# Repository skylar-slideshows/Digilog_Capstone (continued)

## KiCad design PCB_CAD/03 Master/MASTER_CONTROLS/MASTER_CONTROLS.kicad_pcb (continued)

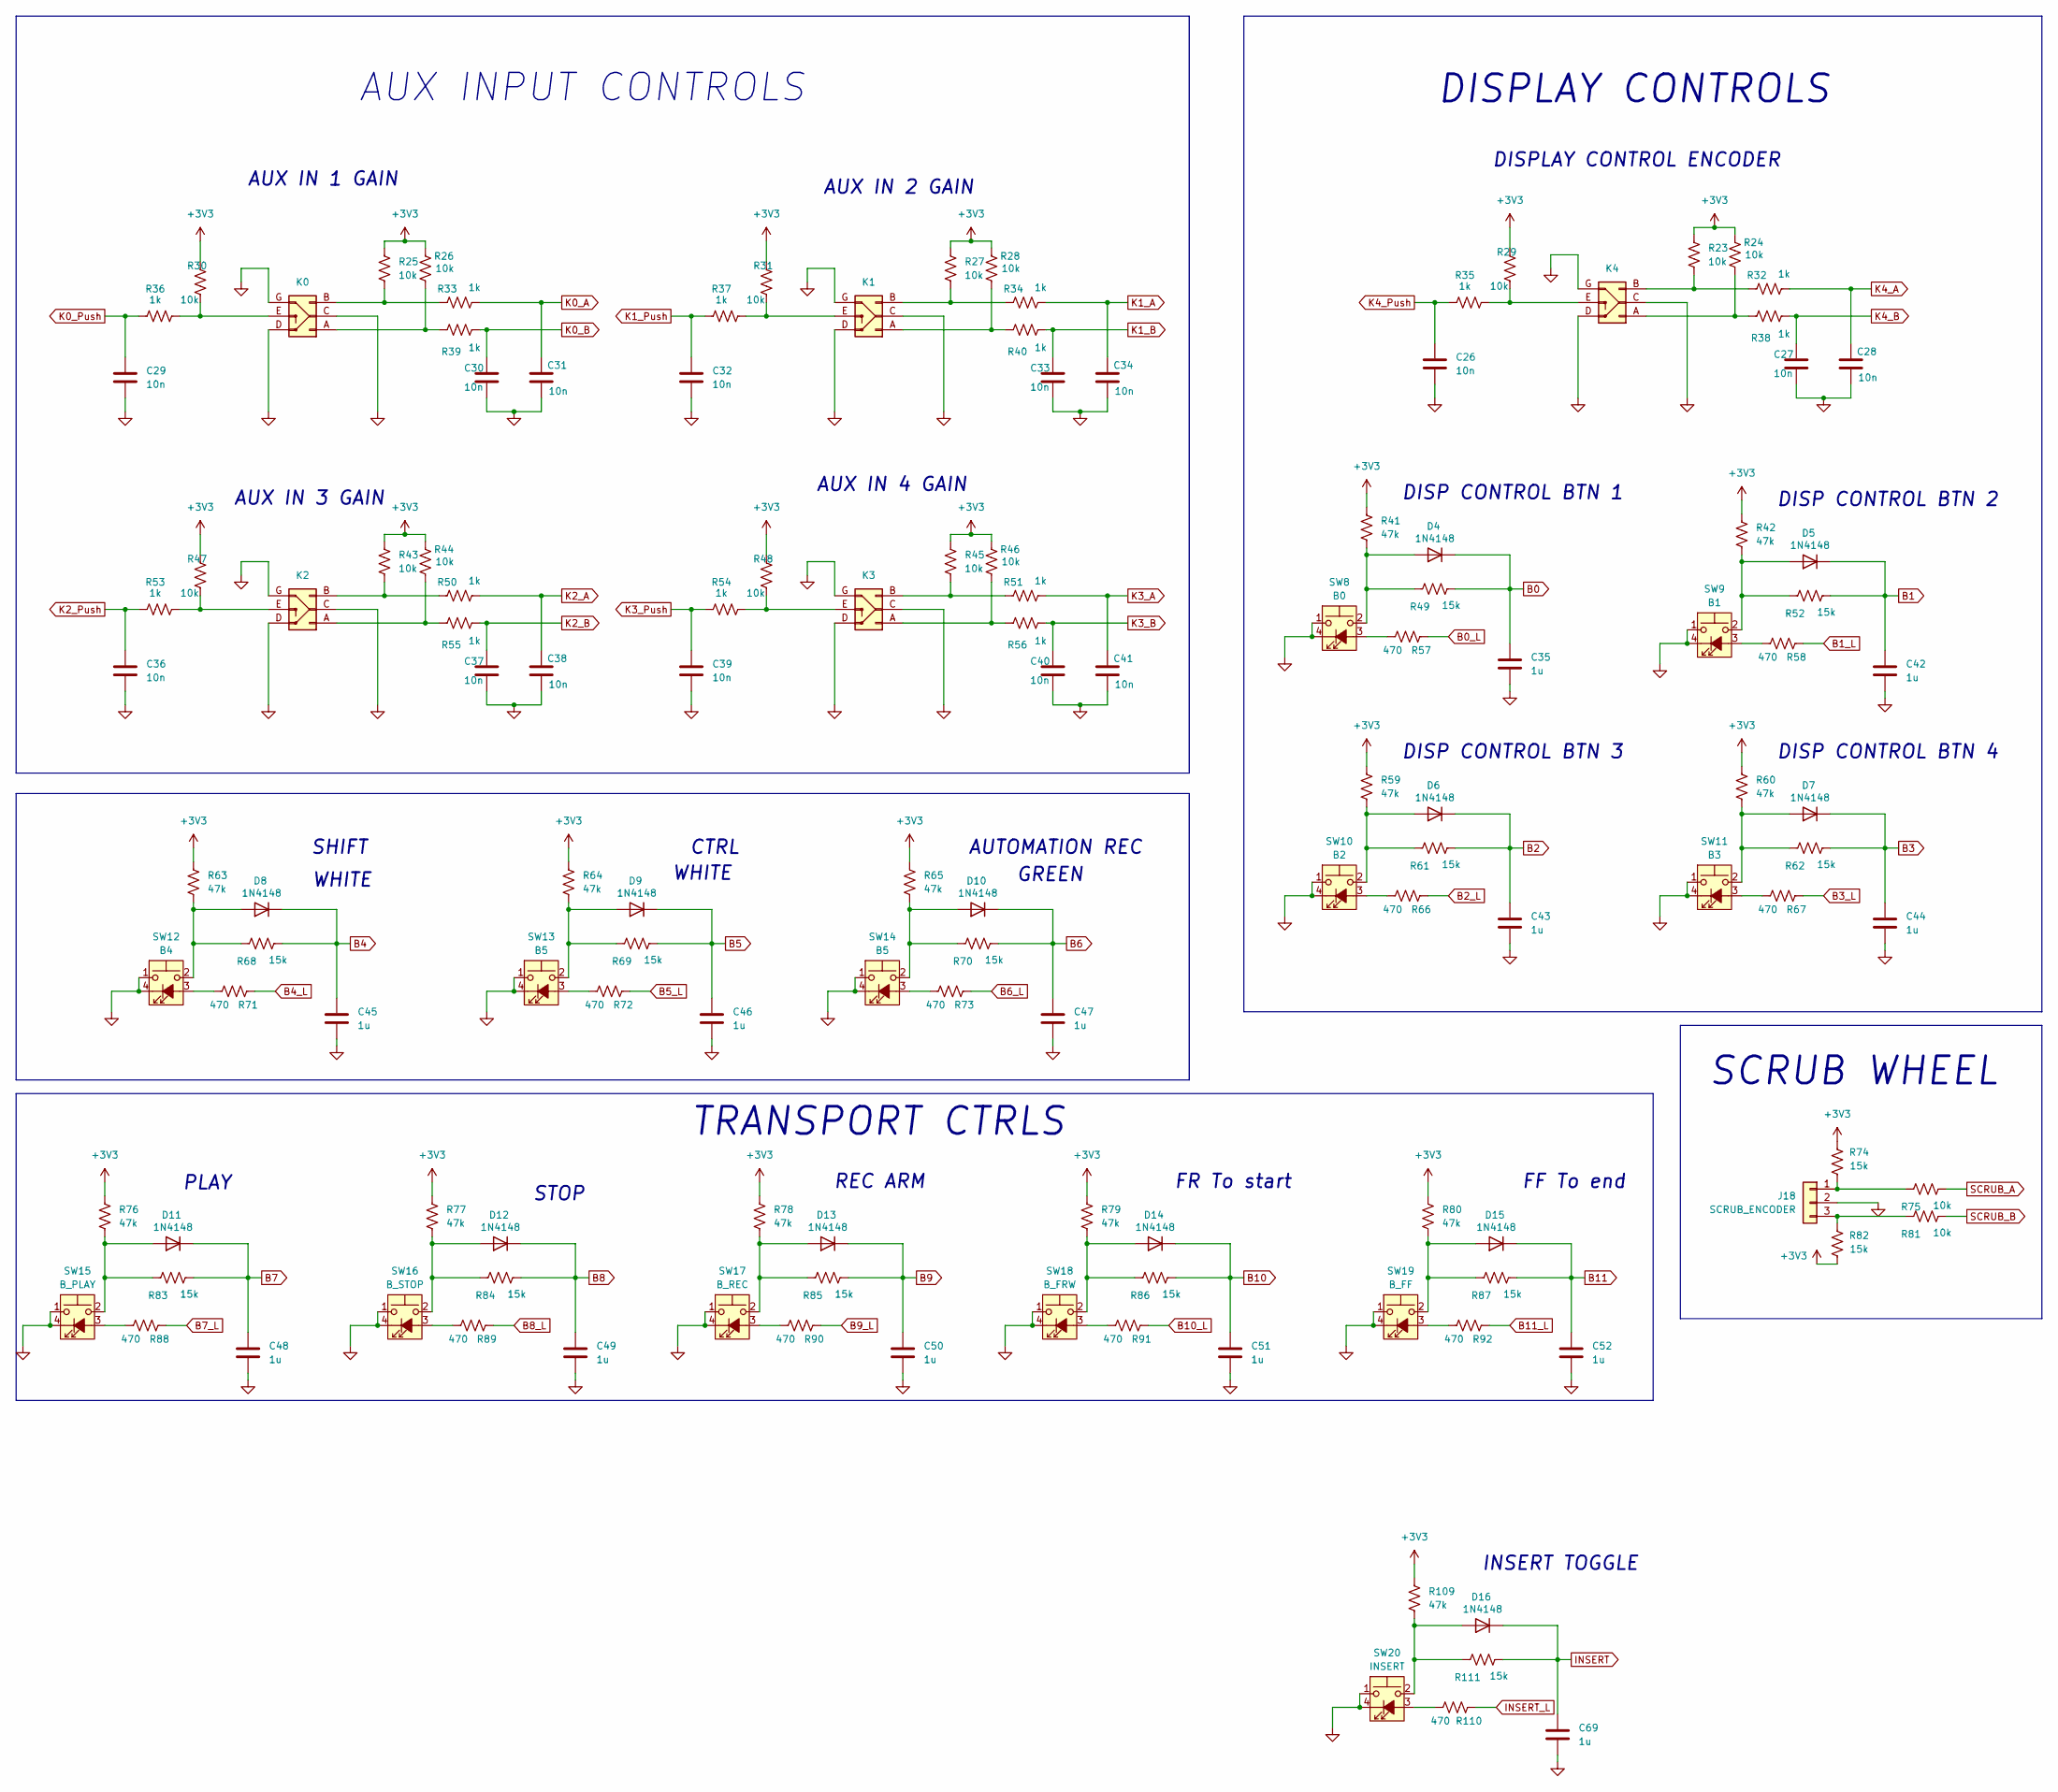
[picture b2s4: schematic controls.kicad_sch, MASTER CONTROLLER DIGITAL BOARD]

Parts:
C26, C27, C28, C29, C30, C31, C32, C33, C34, C36, C37, C38, C39, C40, C41: 10n; C_0402_1005Metric; LCSC C1524
C35, C42, C43, C44, C45, C46, C47, C48, C49, C50, C51, C52, C69: 1u; C_0603_1608Metric; LCSC C15849
D4, D5, D6, D7, D8, D9, D10, D11, D12, D13, D14, D15, D16: 1N4148; D_SOD-323; LCSC C2128
J18: SCRUB_ENCODER; PinHeader_1x03_P2.54mm_Vertical; Part Number 1-0301FBV0T; LCSC DNP
R23, R24, R25, R26, R27, R28, R29, R30, R31, R43, R44, R45, R46, R47, R48, R75, R81: 10k; R_0603_1608Metric; LCSC C25804
R32, R33, R34, R35, R36, R37, R38, R39, R40, R50, R51, R53, R54, R55, R56: 1k; R_0603_1608Metric; LCSC C21190
R41, R42, R59, R60, R63, R64, R65, R76, R77, R78, R79, R80, R109: 47k; R_0603_1608Metric; LCSC C25819
R49, R52, R61, R62, R68, R69, R70, R74, R82, R83, R84, R85, R86, R87, R111: 15k; R_0603_1608Metric; LCSC C22809
R57, R58, R66, R67, R71, R72, R73, R88, R89, R90, R91, R92, R110: 470; R_0603_1608Metric; LCSC C25241
SW3: K4; EC11J0924411; LCSC DNP
SW4: K0; EC11J0924411; LCSC DNP
SW5: K1; EC11J0924411; LCSC DNP
SW6: K2; EC11J0924411; LCSC DNP
SW7: K3; EC11J0924411; LCSC DNP
SW8: B0; CFPB-1CC-4W6_LOWPROF; LCSC DNP
SW9: B1; CFPB-1CC-4W6_LOWPROF; LCSC DNP
SW10: B2; CFPB-1CC-4W6_LOWPROF; LCSC DNP
SW11: B3; CFPB-1CC-4W6_LOWPROF; LCSC DNP
SW12: B4; CFPB-1CC-4W6_LOWPROF; LCSC DNP
SW13, SW14: B5; CFPB-1CC-4W6_LOWPROF; LCSC DNP
SW15: B_PLAY; CFPB-1CC-4W2; LCSC DNP
SW16: B_STOP; CFPB-1CC-4W2; LCSC DNP
SW17: B_REC; CFPB-1CC-4W2; LCSC DNP
SW18: B_FRW; CFPB-1CC-4W2; LCSC DNP
SW19: B_FF; CFPB-1CC-4W2; LCSC DNP
SW20: INSERT; CFPB-1CC-4W6_LOWPROF; LCSC DNP

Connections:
+3V3: R23.1, R24.1, R25.1, R26.1, R27.1, R28.1, R29.1, R30.1, R31.1, R41.1, R42.1, R43.1, R44.1, R45.1, R46.1, R47.1, R48.1, R59.1, R60.1, R63.1, R64.1, R65.1, R74.2, R76.1, R77.1, R78.1, R79.1, R80.1, R82.1, R109.1; also elsewhere on the board
B0: C35.1, D4.1 (K), R49.2; also elsewhere on the board
B0_L: R57.2; also elsewhere on the board
B1: C42.1, D5.1 (K), R52.2; also elsewhere on the board
B1_L: R58.2; also elsewhere on the board
B2: C43.1, D6.1 (K), R61.2; also elsewhere on the board
B2_L: R66.2; also elsewhere on the board
B3: C44.1, D7.1 (K), R62.2; also elsewhere on the board
B3_L: R67.2; also elsewhere on the board
B4: C45.1, D8.1 (K), R68.2; also elsewhere on the board
B4_L: R71.2; also elsewhere on the board
B5: C46.1, D9.1 (K), R69.2; also elsewhere on the board
B5_L: R72.2; also elsewhere on the board
B6: C47.1, D10.1 (K), R70.2; also elsewhere on the board
B6_L: R73.2; also elsewhere on the board
B7: C48.1, D11.1 (K), R83.2; also elsewhere on the board
B7_L: R88.2; also elsewhere on the board
B8: C49.1, D12.1 (K), R84.2; also elsewhere on the board
B8_L: R89.2; also elsewhere on the board
B9: C50.1, D13.1 (K), R85.2; also elsewhere on the board
B9_L: R90.2; also elsewhere on the board
B10: C51.1, D14.1 (K), R86.2; also elsewhere on the board
B10_L: R91.2; also elsewhere on the board
B11: C52.1, D15.1 (K), R87.2; also elsewhere on the board
B11_L: R92.2; also elsewhere on the board
GND: C26.2, C27.2, C28.2, C29.2, C30.2, C31.2, C32.2, C33.2, C34.2, C35.2, C36.2, C37.2, C38.2, C39.2, C40.2, C41.2, C42.2, C43.2, C44.2, C45.2, C46.2, C47.2, C48.2, C49.2, C50.2, C51.2, C52.2, C69.2, J18.2, SW3.C (Pin_2), SW3.D (Pin_4), SW3.G (Pin_6), SW4.C (Pin_2), SW4.D (Pin_4), SW4.G (Pin_6), SW5.C (Pin_2), SW5.D (Pin_4), SW5.G (Pin_6), SW6.C (Pin_2), SW6.D (Pin_4), SW6.G (Pin_6), SW7.C (Pin_2), SW7.D (Pin_4), SW7.G (Pin_6), SW8.1, SW8.4 (K), SW9.1, SW9.4 (K), SW10.1, SW10.4 (K), SW11.1, SW11.4 (K), SW12.1, SW12.4 (K), SW13.1, SW13.4 (K), SW14.1, SW14.4 (K), SW15.1, SW15.4 (K), SW16.1, SW16.4 (K), SW17.1, SW17.4 (K), SW18.1, SW18.4 (K), SW19.1, SW19.4 (K), SW20.1, SW20.4 (K); also elsewhere on the board
INSERT: C69.1, D16.1 (K), R111.2; also elsewhere on the board
INSERT_L: R110.2; also elsewhere on the board
K0_A: C31.1, R33.2; also elsewhere on the board
K0_B: C30.1, R39.2; also elsewhere on the board
K0_Push: C29.1, R36.1; also elsewhere on the board
K1_A: C34.1, R34.2; also elsewhere on the board
K1_B: C33.1, R40.2; also elsewhere on the board
K1_Push: C32.1, R37.1; also elsewhere on the board
K2_A: C38.1, R50.2; also elsewhere on the board
K2_B: C37.1, R55.2; also elsewhere on the board
K2_Push: C36.1, R53.1; also elsewhere on the board
K3_A: C41.1, R51.2; also elsewhere on the board
K3_B: C40.1, R56.2; also elsewhere on the board
K3_Push: C39.1, R54.1; also elsewhere on the board
K4_A: C28.1, R32.2; also elsewhere on the board
K4_B: C27.1, R38.2; also elsewhere on the board
K4_Push: C26.1, R35.1; also elsewhere on the board
unnamed: D4.2 (A), R41.2, R49.1, SW8.2
unnamed: D5.2 (A), R42.2, R52.1, SW9.2
unnamed: D6.2 (A), R59.2, R61.1, SW10.2
unnamed: D7.2 (A), R60.2, R62.1, SW11.2
unnamed: D8.2 (A), R63.2, R68.1, SW12.2
unnamed: D9.2 (A), R64.2, R69.1, SW13.2
unnamed: D10.2 (A), R65.2, R70.1, SW14.2
unnamed: D11.2 (A), R76.2, R83.1, SW15.2
unnamed: D12.2 (A), R77.2, R84.1, SW16.2
unnamed: D13.2 (A), R78.2, R85.1, SW17.2
unnamed: D14.2 (A), R79.2, R86.1, SW18.2
unnamed: D15.2 (A), R80.2, R87.1, SW19.2
unnamed: D16.2 (A), R109.2, R111.1, SW20.2
unnamed: J18.1, R74.1, R75.1
unnamed: J18.3, R81.1, R82.2
unnamed: R24.2, R38.1, SW3.A (Pin_1)
unnamed: R23.2, R32.1, SW3.B (Pin_3)
unnamed: R29.2, R35.2, SW3.E (Pin_5)
unnamed: R26.2, R39.1, SW4.A (Pin_1)
unnamed: R25.2, R33.1, SW4.B (Pin_3)
unnamed: R30.2, R36.2, SW4.E (Pin_5)
unnamed: R28.2, R40.1, SW5.A (Pin_1)
unnamed: R27.2, R34.1, SW5.B (Pin_3)
unnamed: R31.2, R37.2, SW5.E (Pin_5)
unnamed: R44.2, R55.1, SW6.A (Pin_1)
unnamed: R43.2, R50.1, SW6.B (Pin_3)
unnamed: R47.2, R53.2, SW6.E (Pin_5)
unnamed: R46.2, R56.1, SW7.A (Pin_1)
unnamed: R45.2, R51.1, SW7.B (Pin_3)
unnamed: R48.2, R54.2, SW7.E (Pin_5)
unnamed: R57.1, SW8.3 (A)
unnamed: R58.1, SW9.3 (A)
unnamed: R66.1, SW10.3 (A)
unnamed: R67.1, SW11.3 (A)
unnamed: R71.1, SW12.3 (A)
unnamed: R72.1, SW13.3 (A)
unnamed: R73.1, SW14.3 (A)
unnamed: R88.1, SW15.3 (A)
unnamed: R89.1, SW16.3 (A)
unnamed: R90.1, SW17.3 (A)
unnamed: R91.1, SW18.3 (A)
unnamed: R92.1, SW19.3 (A)
unnamed: R110.1, SW20.3 (A)
SCRUB_A: R75.2; also elsewhere on the board
SCRUB_B: R81.2; also elsewhere on the board

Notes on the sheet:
DISP CONTROL BTN 4
WHITE
AUTOMATION REC
AUX IN 4 GAIN
STOP
TRANSPORT CTRLS
AUX IN 2 GAIN
SCRUB WHEEL
CTRL
FR To start
SHIFT
DISP CONTROL BTN 2
REC ARM
AUX INPUT CONTROLS
INSERT TOGGLE
GREEN
DISP CONTROL BTN 3
PLAY
AUX IN 3 GAIN
AUX IN 1 GAIN
DISPLAY CONTROLS
DISPLAY CONTROL ENCODER
DISP CONTROL BTN 1
FF To end

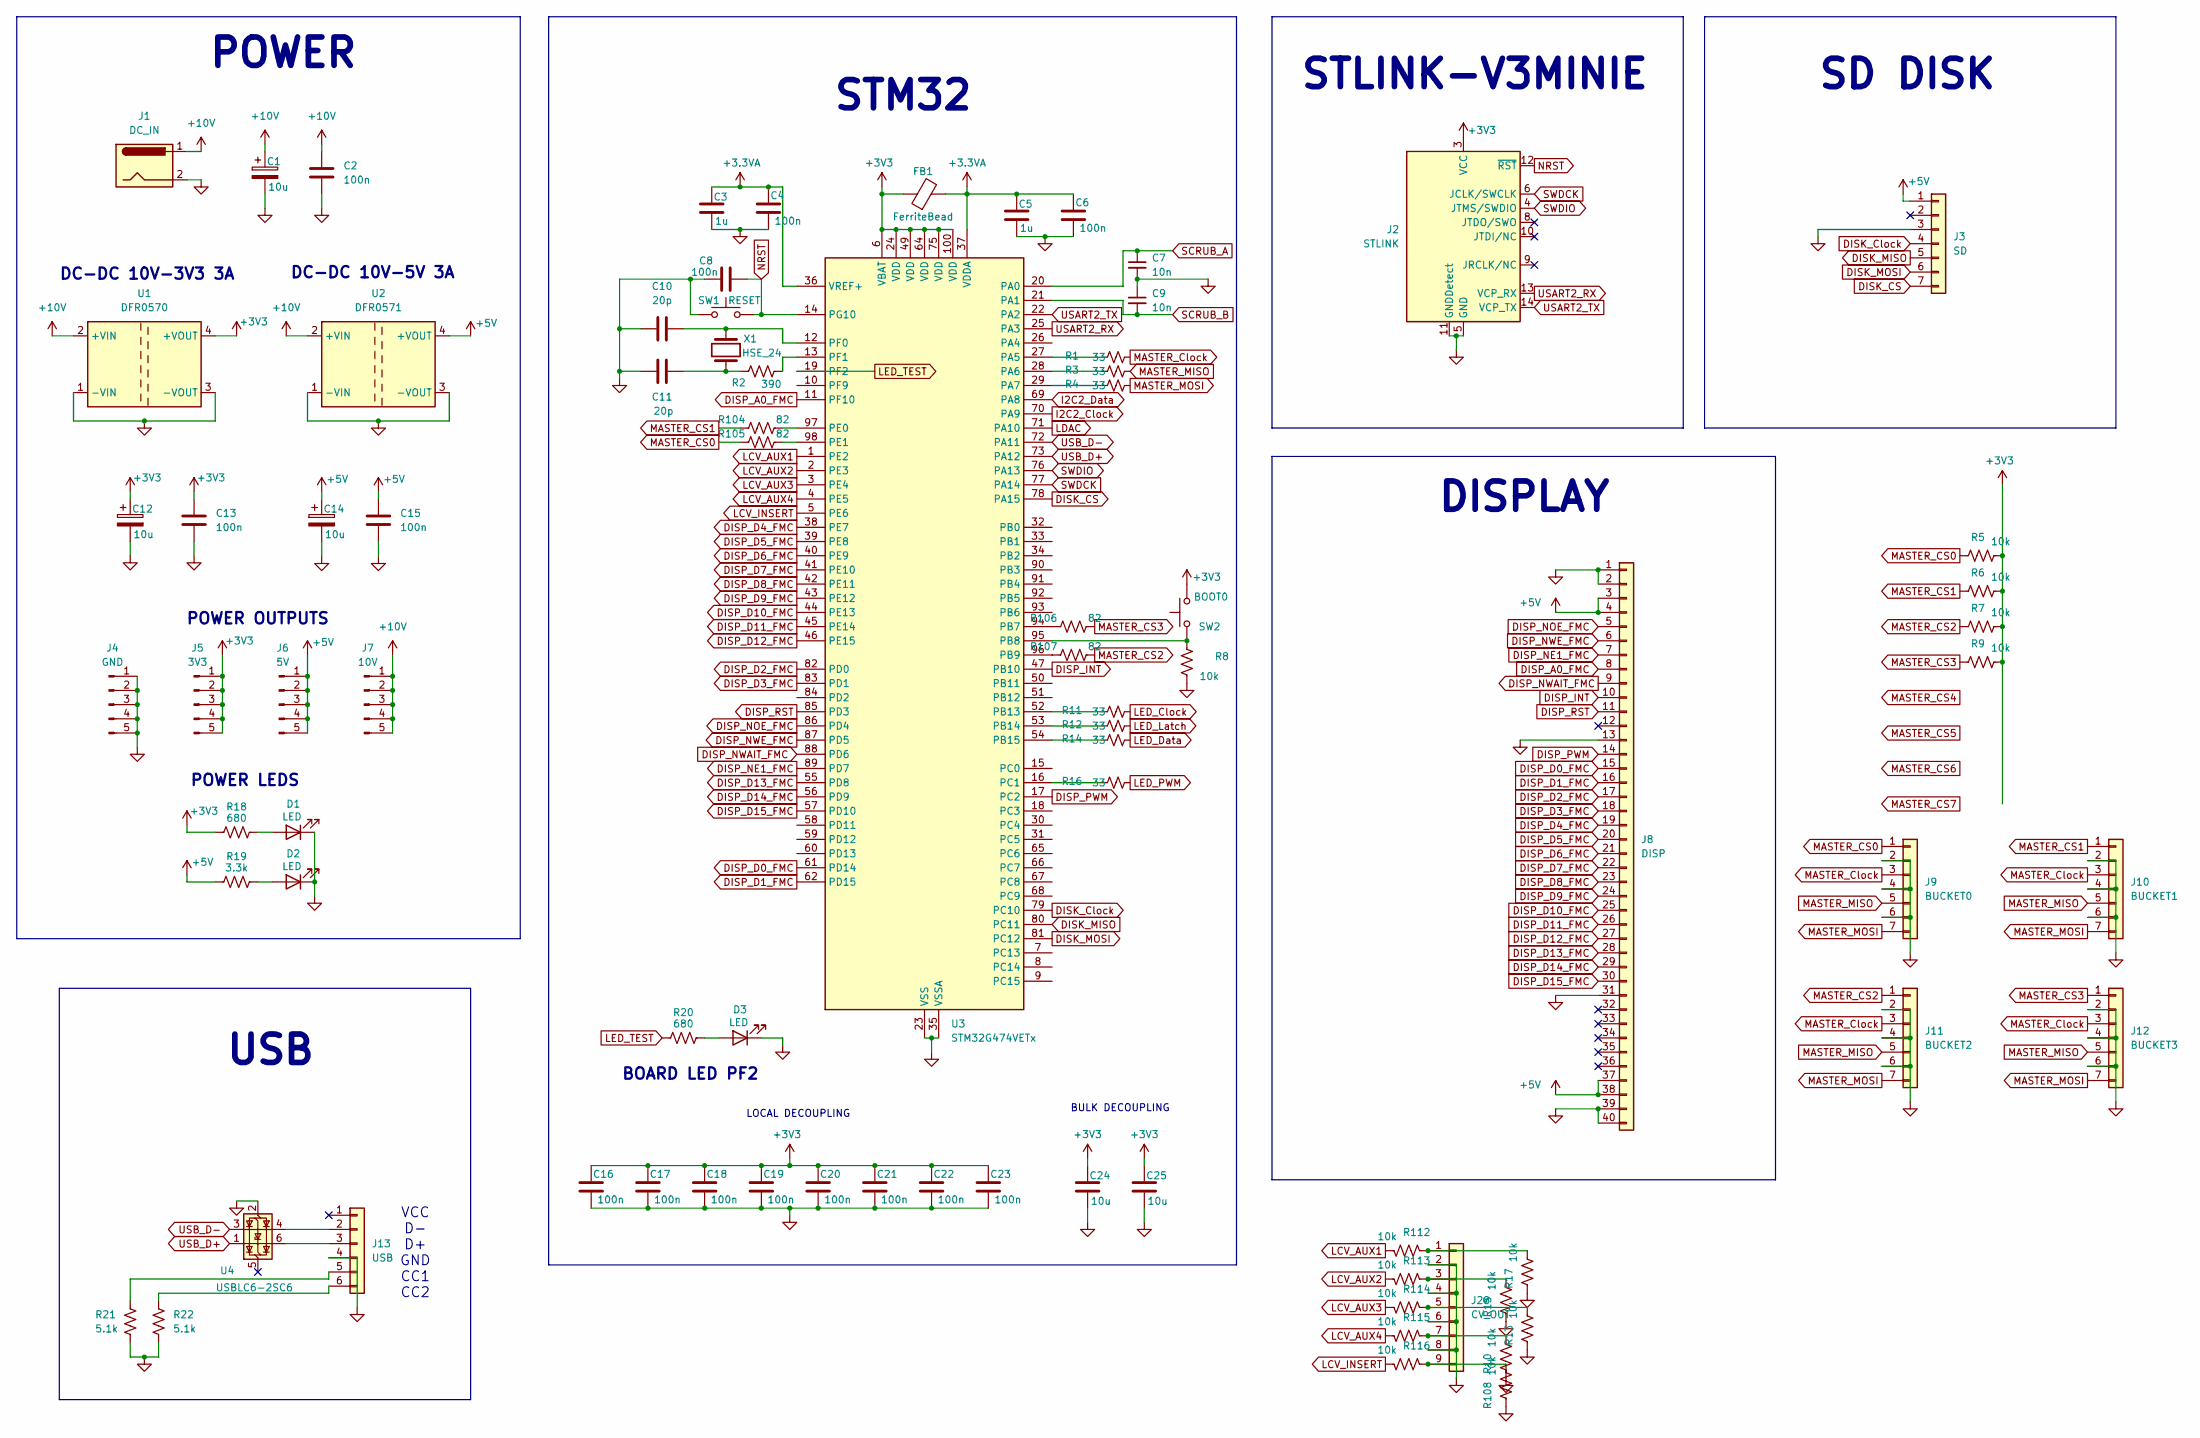
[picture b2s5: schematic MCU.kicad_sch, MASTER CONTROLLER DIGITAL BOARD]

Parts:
C1, C12, C14, C24, C25: 10u; C_1206_3216Metric; LCSC C1849
C2, C4, C6, C8, C13, C15, C16, C17, C18, C19, C20, C21, C22, C23: 100n; C_0603_1608Metric; LCSC C1590
C3, C5: 1u; C_0603_1608Metric; LCSC C15849
C7, C9: 10n; C_0402_1005Metric; LCSC C1524
C10, C11: 20p; C_0603_1608Metric; LCSC C1648
D1, D2, D3: LED; LED_0603_1608Metric; LCSC C12065
FB1: FerriteBead; Ferrite_0603_1608Metric; LCSC C1002
J1: DC_IN; BarrelJack_Horizontal; LCSC DNP
J2: STLINK; FTSH-107-01-L-DV-K-TR; LCSC C5307809
J3: SD; PinHeader_1x07_P2.54mm_Vertical; LCSC DNP
J4: GND; PinSocket_1x05_P2.54mm_Vertical; LCSC DNP
J5: 3V3; PinSocket_1x05_P2.54mm_Vertical; LCSC DNP
J6: 5V; PinSocket_1x05_P2.54mm_Vertical; LCSC DNP
J7: 10V; PinSocket_1x05_P2.54mm_Vertical; LCSC DNP
J8: DISP; GCT_FFC3B07-40-T; LCSC DNP
J9: BUCKET0; PinHeader_1x07_P2.54mm_Vertical; LCSC DNP
J10: BUCKET1; PinHeader_1x07_P2.54mm_Vertical; LCSC DNP
J11: BUCKET2; PinHeader_1x07_P2.54mm_Vertical; LCSC DNP
J12: BUCKET3; PinHeader_1x07_P2.54mm_Vertical; LCSC DNP
J13: USB; PinHeader_1x06_P2.00mm_Vertical; Part Number 1-0601FBV0T; LCSC dnp
J28: CV_OUT; PinHeader_1x09_P2.54mm_Vertical; LCSC DNP
R1, R3, R4, R11, R12, R14, R16: 33; R_0603_1608Metric; LCSC C23140
R2: 390; R_1206_3216Metric; LCSC C4491
R5, R6, R7, R8, R9, R10, R13, R15, R17, R108: 10k; R_0603_1608Metric; LCSC C25804
R18, R20: 680; R_0603_1608Metric; LCSC C23228
R19: 3.3k; R_0603_1608Metric; LCSC C22978
R21, R22: 5.1k; R_0603_1608Metric; LCSC C14677
R104, R105, R106, R107: 82; R_0603_1608Metric; LCSC C23255
R112, R113, R114, R115, R116: 10k; R_0603_1608Metric; LCSC C21190
SW1: RESET; SW_Push_1P1T_NO_CK_KMR2; LCSC C72443
SW2: BOOT0; SW_Push_1P1T_NO_CK_KMR2; LCSC C72443
U1: DFR0570; DFR05xx_DC-DC; LCSC DNP
U2: DFR0571; DFR05xx_DC-DC; LCSC DNP
U3: STM32G474VETx; LQFP-100_14x14mm_P0.5mm; LCSC C2970837
U4: USBLC6-2SC6; SOT-23-6; LCSC C7519
X1: HSE_24; Crystal_SMD_HC49-SD; LCSC C2253

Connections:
+3.3VA: C3.1, C4.1, C5.1, C6.1, FB1.2, U3.36 (VREF+), U3.37 (VDDA)
+3V3: C12.1, C13.1, C16.1, C17.1, C18.1, C19.1, C20.1, C21.1, C22.1, C23.1, C24.1, C25.1, FB1.1, J2.3 (VCC), J5.1, J5.2, J5.3, J5.4, J5.5, R5.2, R6.2, R7.2, R9.2, R18.1, SW2.2, U1.4 (+VOUT), U3.6 (VBAT), U3.24 (VDD), U3.49 (VDD), U3.64 (VDD), U3.75 (VDD), U3.100 (VDD); also elsewhere on the board
+5V: C14.1, C15.1, J3.1, J6.1, J6.2, J6.3, J6.4, J6.5, J8.3, J8.4, J8.37, J8.38, R19.1, U2.4 (+VOUT); also elsewhere on the board
+10V: C1.1, C2.1, J1.1, J7.1, J7.2, J7.3, J7.4, J7.5, U1.2 (+VIN), U2.2 (+VIN)
DISK_CS: J3.7, U3.78 (PA15)
DISK_Clock: J3.4, U3.79 (PC10)
DISK_MISO: J3.5, U3.80 (PC11)
DISK_MOSI: J3.6, U3.81 (PC12)
DISP_A0_FMC: J8.8, U3.11 (PF10)
DISP_D0_FMC: J8.15, U3.61 (PD14)
DISP_D1_FMC: J8.16, U3.62 (PD15)
DISP_D2_FMC: J8.17, U3.82 (PD0)
DISP_D3_FMC: J8.18, U3.83 (PD1)
DISP_D4_FMC: J8.19, U3.38 (PE7)
DISP_D5_FMC: J8.20, U3.39 (PE8)
DISP_D6_FMC: J8.21, U3.40 (PE9)
DISP_D7_FMC: J8.22, U3.41 (PE10)
DISP_D8_FMC: J8.23, U3.42 (PE11)
DISP_D9_FMC: J8.24, U3.43 (PE12)
DISP_D10_FMC: J8.25, U3.44 (PE13)
DISP_D11_FMC: J8.26, U3.45 (PE14)
DISP_D12_FMC: J8.27, U3.46 (PE15)
DISP_D13_FMC: J8.28, U3.55 (PD8)
DISP_D14_FMC: J8.29, U3.56 (PD9)
DISP_D15_FMC: J8.30, U3.57 (PD10)
DISP_INT: J8.10, U3.47 (PB10)
DISP_NE1_FMC: J8.7, U3.89 (PD7)
DISP_NOE_FMC: J8.5, U3.86 (PD4)
DISP_NWAIT_FMC: J8.9, U3.88 (PD6)
DISP_NWE_FMC: J8.6, U3.87 (PD5)
DISP_PWM: J8.14, U3.17 (PC2)
DISP_RST: J8.11, U3.85 (PD3)
GND: C1.2, C2.2, C3.2, C4.2, C5.2, C6.2, C7.2, C8.1, C9.1, C10.2, C11.1, C12.2, C13.2, C14.2, C15.2, C16.2, C17.2, C18.2, C19.2, C20.2, C21.2, C22.2, C23.2, C24.2, C25.2, D1.1 (K), D2.1 (K), D3.1 (K), J1.2, J2.5 (GND), J2.7 (GND), J2.11 (GNDDetect), J3.3, J4.1, J4.2, J4.3, J4.4, J4.5, J8.1, J8.2, J8.13, J8.31, J8.39, J8.40, J9.2, J9.4, J9.6, J10.2, J10.4, J10.6, J11.2, J11.4, J11.6, J12.2, J12.4, J12.6, J13.4, J28.2, J28.4, J28.6, J28.8, R8.1, R10.1, R13.1, R15.1, R17.1, R21.1, R22.1, R108.1, SW1.1, U1.1 (-VIN), U1.3 (-VOUT), U2.1 (-VIN), U2.3 (-VOUT), U3.23 (VSS), U3.35 (VSSA), U3.48 (VSS), U3.63 (VSS), U3.74 (VSS), U3.99 (VSS), U4.2 (GND); also elsewhere on the board
I2C2_Clock: U3.70 (PA9); also elsewhere on the board
I2C2_Data: U3.69 (PA8); also elsewhere on the board
LCV_AUX1: R112.2, U3.1 (PE2)
LCV_AUX2: R113.2, U3.2 (PE3)
LCV_AUX3: R114.2, U3.3 (PE4)
LCV_AUX4: R115.2, U3.4 (PE5)
LCV_INSERT: R116.2, U3.5 (PE6)
LDAC: U3.71 (PA10); also elsewhere on the board
LED_Clock: R11.2; also elsewhere on the board
LED_Data: R14.2; also elsewhere on the board
LED_Latch: R12.2; also elsewhere on the board
LED_PWM: R16.2; also elsewhere on the board
LED_TEST: R20.1, U3.19 (PF2)
MASTER_CS0: J9.1, R5.1, R105.1
MASTER_CS1: J10.1, R6.1, R104.1
MASTER_CS2: J11.1, R7.1, R107.2
MASTER_CS3: J12.1, R9.1, R106.2
MASTER_Clock: J9.3, J10.3, J11.3, J12.3, R1.2
MASTER_MISO: J9.5, J10.5, J11.5, J12.5, R3.2
MASTER_MOSI: J9.7, J10.7, J11.7, J12.7, R4.2
NRST: C8.2, J2.12 (~RST), SW1.2, U3.14 (PG10)
unnamed: C11.2, R2.1, X1.2
unnamed: D1.2 (A), R18.2
unnamed: D2.2 (A), R19.2
unnamed: D3.2 (A), R20.2
unnamed: J13.2, U4.4 (I/O2)
unnamed: J13.3, U4.6 (I/O1)
unnamed: J13.5, R21.2
unnamed: J13.6, R22.2
unnamed: J28.1, R17.2, R112.1
unnamed: J28.3, R15.2, R113.1
unnamed: J28.5, R13.2, R114.1
unnamed: J28.7, R10.2, R115.1
unnamed: J28.9, R108.2, R116.1
unnamed: R1.1, U3.27 (PA5)
unnamed: R3.1, U3.28 (PA6)
unnamed: R4.1, U3.29 (PA7)
unnamed: R106.1, U3.94 (PB7)
unnamed: R8.2, SW2.1, U3.95 (PB8)
unnamed: R107.1, U3.96 (PB9)
unnamed: R11.1, U3.52 (PB13)
unnamed: R12.1, U3.53 (PB14)
unnamed: R14.1, U3.54 (PB15)
unnamed: R16.1, U3.16 (PC1)
unnamed: R104.2, U3.97 (PE0)
unnamed: R105.2, U3.98 (PE1)
unnamed: C10.1, U3.12 (PF0), X1.1
unnamed: R2.2, U3.13 (PF1)
SCRUB_A: C7.1, U3.20 (PA0); also elsewhere on the board
SCRUB_B: C9.2, U3.21 (PA1); also elsewhere on the board
SWDCK: J2.6 (JCLK/SWCLK), U3.77 (PA14)
SWDIO: J2.4 (JTMS/SWDIO), U3.76 (PA13)
USART2_RX: J2.13 (VCP_RX), U3.25 (PA3)
USART2_TX: J2.14 (VCP_TX), U3.22 (PA2)
USB_D+: U3.73 (PA12), U4.1 (I/O1)
USB_D-: U3.72 (PA11), U4.3 (I/O2)

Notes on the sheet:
DISPLAY
POWER LEDS
STLINK-V3MINIE
STM32
DC-DC 10V-5V 3A
BULK DECOUPLING
LOCAL DECOUPLING
POWER
BOARD LED PF2
POWER OUTPUTS
DC-DC 10V-3V3 3A
SD DISK
USB
VCC D- D+ GND CC1 CC2

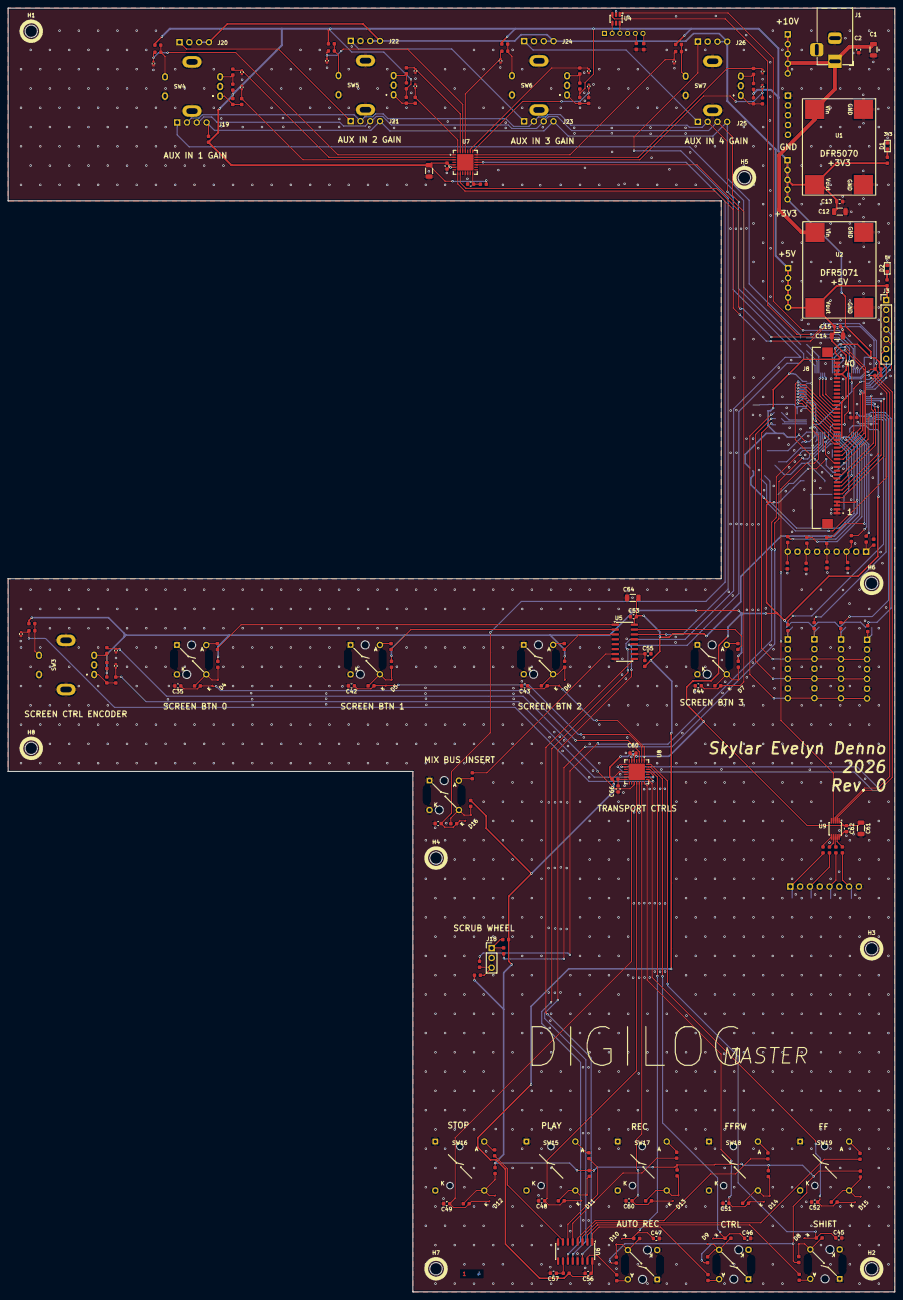
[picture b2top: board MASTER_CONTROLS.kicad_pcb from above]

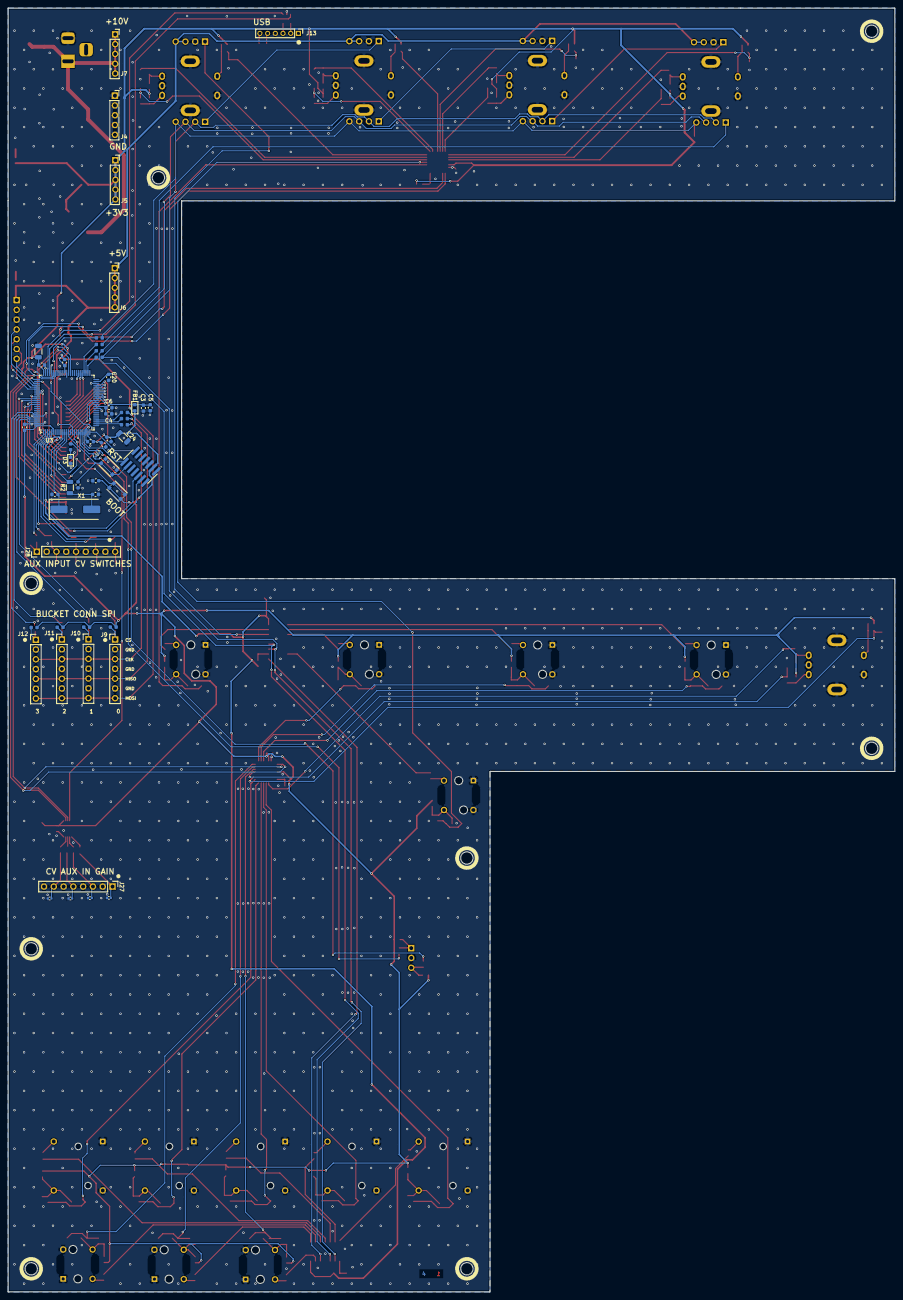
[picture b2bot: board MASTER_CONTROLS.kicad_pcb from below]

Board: 4 copper layers, 230.0 x 333.0 mm, 264 parts (54 on the bottom side), 190 nets.

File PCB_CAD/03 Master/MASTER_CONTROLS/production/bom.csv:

Designator,Footprint,Quantity,Value,LCSC Part #
"C1, C12, C14, C24, C25, C54, C59, C61",1206,8,10u,C1849
"C10, C11",0603,2,20p,C1648
"C13, C15, C16, C17, C18, C19, C2, C20, C21, C22, C23, C4, C53, C55, C56, C57, C58, C6, C60, C62, C65, C66, C8",0603,23,100n,C1590
"C26, C27, C28, C29, C30, C31, C32, C33, C34, C36, C37, C38, C39, C40, C41, C63, C64, C67, C68, C7, C9",0402,21,10n,C1524
"C3, C35, C42, C43, C44, C45, C46, C47, C48, C49, C5, C50, C51, C52, C69",0603,15,1u,C15849
"D1, D2, D3",0603,3,LED,C12065
"D10, D11, D12, D13, D14, D15, D16, D4, D5, D6, D7, D8, D9",D_SOD-323,13,1N4148,C2128
FB1,Ferrite_0603_1608Metric,1,FerriteBead,C1002
J1,BarrelJack_Horizontal,1,DC_IN,DNP
J10,PinHeader_1x07_P2.54mm_Vertical,1,BUCKET1,DNP
J11,PinHeader_1x07_P2.54mm_Vertical,1,BUCKET2,DNP
J12,PinHeader_1x07_P2.54mm_Vertical,1,BUCKET3,DNP
J13,PinHeader_1x06_P2.00mm_Vertical,1,USB,dnp
J18,PinHeader_1x03_P2.54mm_Vertical,1,SCRUB_ENCODER,DNP
"J19, J21, J23, J25",PinSocket_1x04_P2.54mm_Vertical,4,Data,DNP
J2,FTSH-107-01-L-DV-K-TR,1,STLINK,C5307809
"J20, J22, J24, J26",PinSocket_1x04_P2.54mm_Vertical,4,Pow,DNP
J27,PinHeader_1x08_P2.54mm_Vertical,1,CV_OUT,DNP
J28,PinHeader_1x09_P2.54mm_Vertical,1,CV_OUT,DNP
J3,PinHeader_1x07_P2.54mm_Vertical,1,SD,DNP
J4,PinSocket_1x05_P2.54mm_Vertical,1,GND,DNP
J5,PinSocket_1x05_P2.54mm_Vertical,1,3V3,DNP
J6,PinSocket_1x05_P2.54mm_Vertical,1,5V,DNP
J7,PinSocket_1x05_P2.54mm_Vertical,1,10V,DNP
J8,GCT_FFC3B07-40-T,1,DISP,DNP
J9,PinHeader_1x07_P2.54mm_Vertical,1,BUCKET0,DNP
"R1, R11, R12, R14, R16, R3, R4",0603,7,33,C23140
"R10, R100, R108, R13, R15, R17, R23, R24, R25, R26, R27, R28, R29, R30, R31, R43, R44, R45, R46, R47, R48, R5, R6, R7, R75, R8, R81, R9, R93, R94, R95, R99",0603,32,10k,C25804
"R101, R102, R103, R96",0603,4,470,C23179
"R104, R105, R106, R107",0603,4,82,C23255
"R109, R41, R42, R59, R60, R63, R64, R65, R76, R77, R78, R79, R80",0603,13,47k,C25819
"R110, R57, R58, R66, R67, R71, R72, R73, R88, R89, R90, R91, R92",0603,13,470,C25241
"R111, R49, R52, R61, R62, R68, R69, R70, R74, R82, R83, R84, R85, R86, R87",0603,15,15k,C22809
"R112, R113, R114, R115, R116",0603,5,10k,C21190
"R18, R20",0603,2,680,C23228
R19,0603,1,3.3k,C22978
R2,1206,1,390,C4491
"R21, R22",0603,2,5.1k,C14677
"R32, R33, R34, R35, R36, R37, R38, R39, R40, R50, R51, R53, R54, R55, R56",0603,15,1k,C21190
"R97, R98",0603,2,1.5k,C22843
SW1,SW_Push_1P1T_NO_CK_KMR2,1,RESET,C72443
SW10,CFPB-1CC-4W6_LOWPROF,1,B2,DNP
SW11,CFPB-1CC-4W6_LOWPROF,1,B3,DNP
SW12,CFPB-1CC-4W6_LOWPROF,1,B4,DNP
"SW13, SW14",CFPB-1CC-4W6_LOWPROF,2,B5,DNP
SW15,CFPB-1CC-4W2,1,B_PLAY,DNP
SW16,CFPB-1CC-4W2,1,B_STOP,DNP
SW17,CFPB-1CC-4W2,1,B_REC,DNP
SW18,CFPB-1CC-4W2,1,B_FRW,DNP
SW19,CFPB-1CC-4W2,1,B_FF,DNP
SW2,SW_Push_1P1T_NO_CK_KMR2,1,BOOT0,C72443
SW20,CFPB-1CC-4W6_LOWPROF,1,INSERT,DNP
SW3,EC11J0924411,1,K4,DNP
SW4,EC11J0924411,1,K0,DNP
SW5,EC11J0924411,1,K1,DNP
SW6,EC11J0924411,1,K2,DNP
SW7,EC11J0924411,1,K3,DNP
SW8,CFPB-1CC-4W6_LOWPROF,1,B0,DNP
SW9,CFPB-1CC-4W6_LOWPROF,1,B1,DNP
U1,DFR05xx_DC-DC,1,DFR0570,DNP
U2,DFR05xx_DC-DC,1,DFR0571,DNP
U3,LQFP-100_14x14mm_P0.5mm,1,STM32G474VETx,C2970837
U4,SOT-23-6,1,USBLC6-2SC6,C7519
"U5, U6",SOIC-16_3.9x9.9mm_P1.27mm,2,74HCT595,C282339
U7,QFN-28-1EP_6x6mm_P0.65mm_EP4.25x4.25mm,1,MCP23017_0,C629439
U8,QFN-28-1EP_6x6mm_P0.65mm_EP4.25x4.25mm,1,MCP23017_1,C629439
U9,MSOP-10_3x3mm_P0.5mm,1,MCP4728,C108207
X1,Crystal_SMD_HC49-SD,1,HSE_24,C2253
